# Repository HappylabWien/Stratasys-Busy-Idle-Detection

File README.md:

# Stratasys-Busy-Idle-Detection
Script and eagle files to set up a Raspberry Pi to detect if a Stratasys 3D Printer in the Network is Busy at the moment and to relais this information to an Fabman Bridge (www.fabman.io) for access control and payment.

Usage at your own Risk!!!!

For a detailed discription see https://forum.fabman.io/t/how-to-connect-fabman-bridge-with-stratasys-3d-printer/85

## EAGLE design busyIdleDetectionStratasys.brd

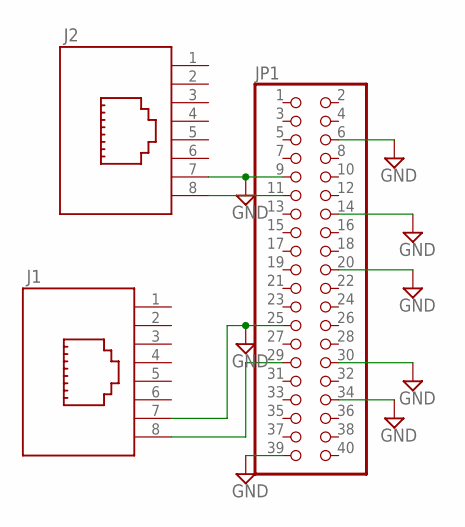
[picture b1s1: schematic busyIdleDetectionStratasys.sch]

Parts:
J1, J2: 634008137221
JP1: PINHD-2X20; 2X20

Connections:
GND: J1.7 (2), J2.7 (2), JP1.6, JP1.9, JP1.14, JP1.20, JP1.25, JP1.30, JP1.34, JP1.39
unnamed: J2.8 (1), JP1.11
unnamed: J1.8 (1), JP1.29

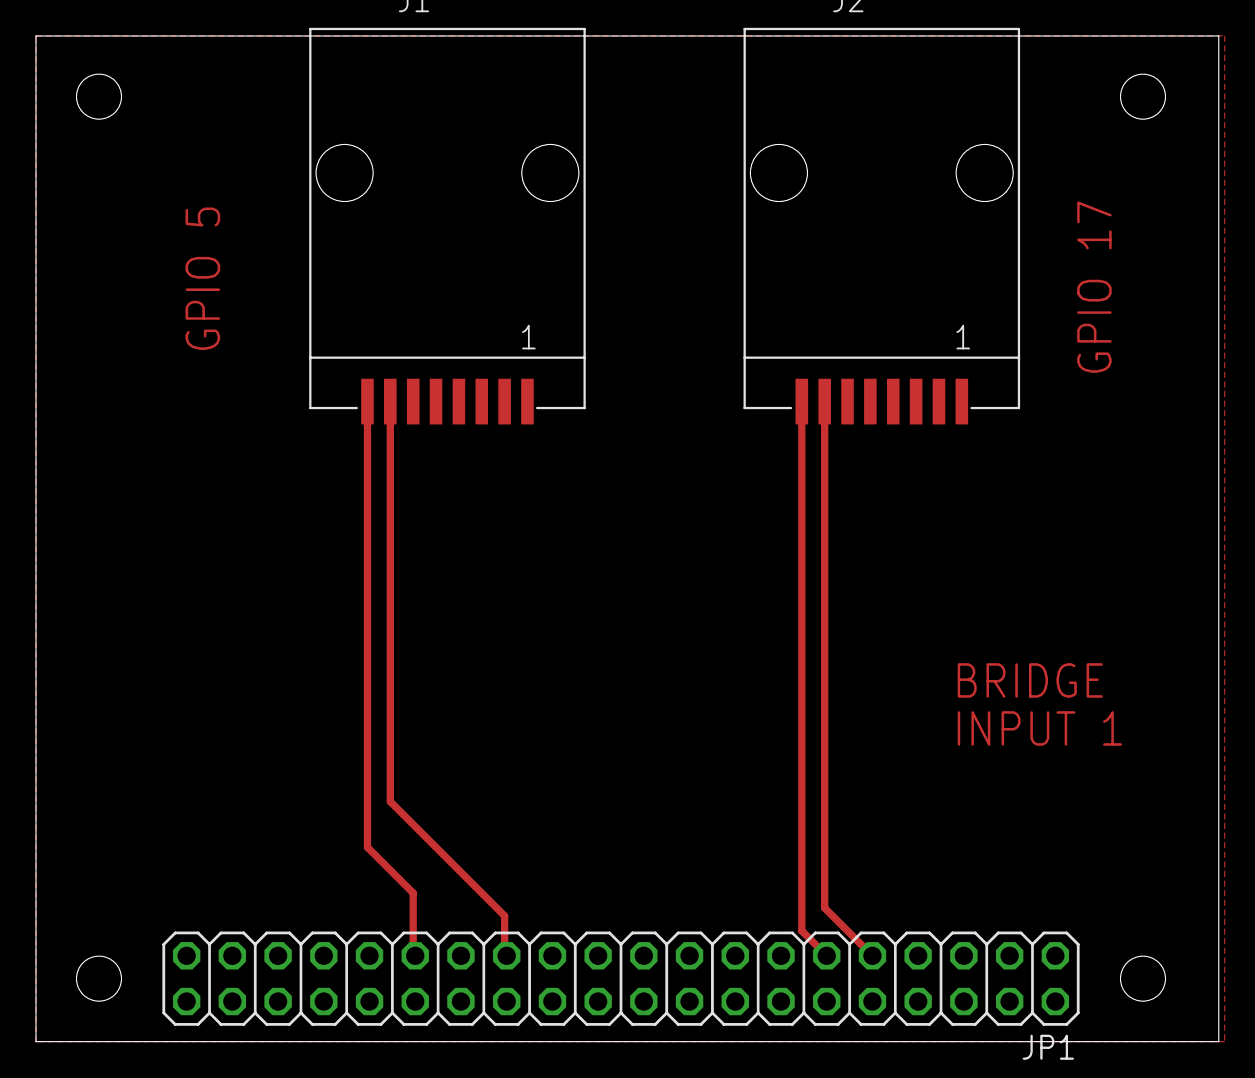
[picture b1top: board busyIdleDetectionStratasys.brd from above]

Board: 2 copper layers, 65.7 x 55.9 mm, 3 parts (0 on the bottom side), 3 nets.

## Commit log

2018-01-12 added shell scripts

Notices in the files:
parts and their libraries:
EAGLE-INPUT_OUTPUT_CONNECTORS-rev17d: Copyright: Würth Elektronik
